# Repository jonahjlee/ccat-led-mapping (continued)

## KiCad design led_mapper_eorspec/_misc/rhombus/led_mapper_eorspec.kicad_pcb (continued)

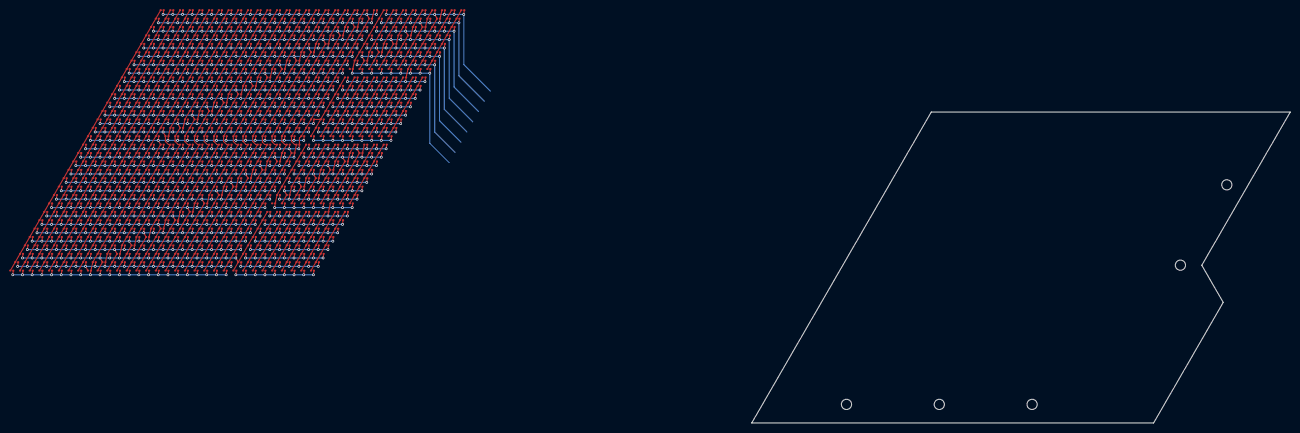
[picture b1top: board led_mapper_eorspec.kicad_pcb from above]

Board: 4 copper layers, 116.0 x 67.0 mm, 1025 parts (1 on the bottom side), 24 nets.

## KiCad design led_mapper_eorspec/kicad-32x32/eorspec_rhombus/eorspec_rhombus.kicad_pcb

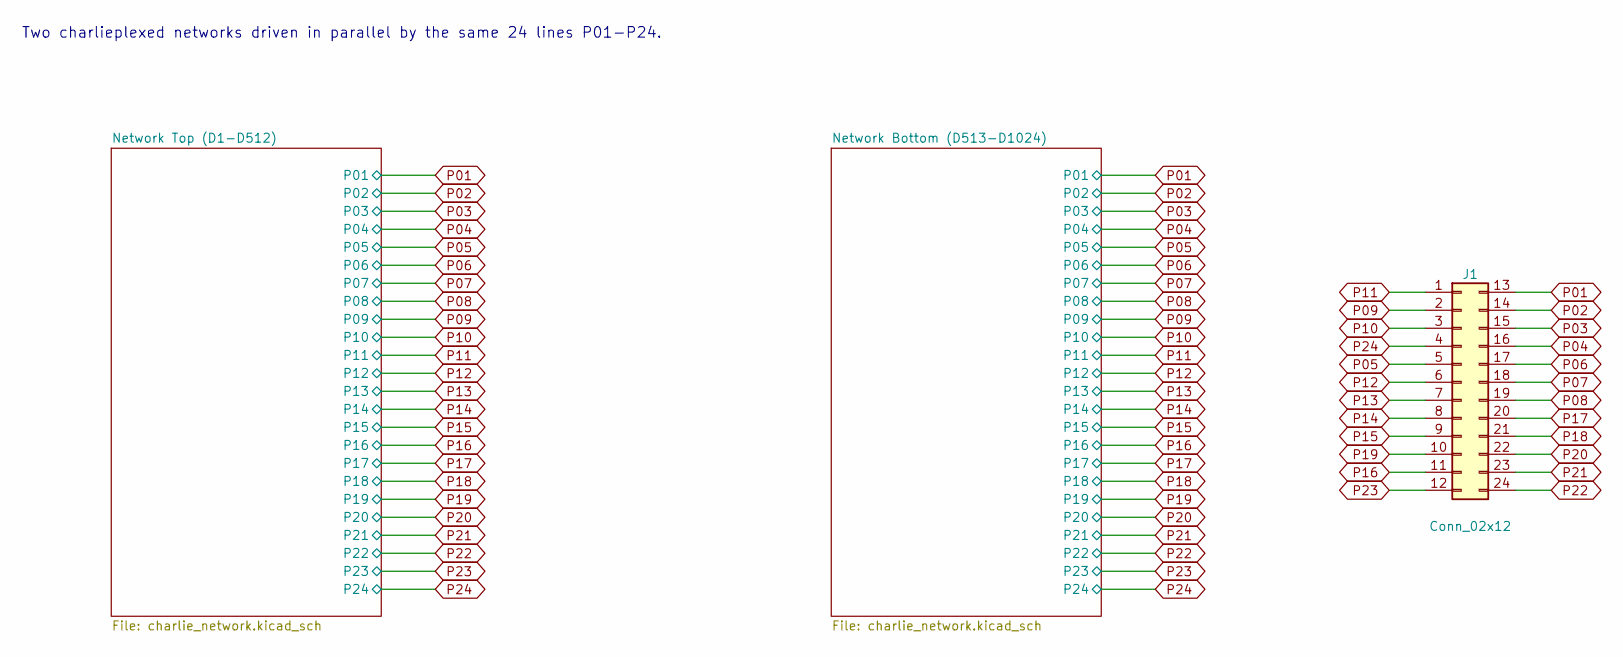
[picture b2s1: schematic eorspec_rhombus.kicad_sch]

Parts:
J1: Conn_02x12; PinSocket_2x12_P2.54mm_Vertical_SMD_custom

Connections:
P01: J1.13; also elsewhere on the board
P02: J1.14; also elsewhere on the board
P03: J1.15; also elsewhere on the board
P04: J1.16; also elsewhere on the board
P05: J1.5; also elsewhere on the board
P06: J1.17; also elsewhere on the board
P07: J1.18; also elsewhere on the board
P08: J1.19; also elsewhere on the board
P09: J1.2; also elsewhere on the board
P10: J1.3; also elsewhere on the board
P11: J1.1; also elsewhere on the board
P12: J1.6; also elsewhere on the board
P13: J1.7; also elsewhere on the board
P14: J1.8; also elsewhere on the board
P15: J1.9; also elsewhere on the board
P16: J1.11; also elsewhere on the board
P17: J1.20; also elsewhere on the board
P18: J1.21; also elsewhere on the board
P19: J1.10; also elsewhere on the board
P20: J1.22; also elsewhere on the board
P21: J1.23; also elsewhere on the board
P22: J1.24; also elsewhere on the board
P23: J1.12; also elsewhere on the board
P24: J1.4; also elsewhere on the board

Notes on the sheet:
Two charlieplexed networks driven in parallel by the same 24 lines P01-P24.
